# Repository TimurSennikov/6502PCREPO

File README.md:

этот репозиторий был создан для моего друга Ромы, чтобы пояснить ему что и куда паять, если вы про и знаете, что такое конденсатор, можете не читать эту часть README.

###обозначения###

общие:
C - конденсатор (на схеме круг с закрашенной правой половиной), накапливает в себе заряд, в схеме нужен для выпрямления высокочастотных колебаний на микросхемах (0.1uF) и на входе (10uF).

R - резистор/сопротивление (на схеме прямоугольник с выводами из меньших сторон) препятствует протеканию тока U=IR, где U - напряжение, I - сила тока, R - сопротивление, в схеме используется для понижения протекающего за резисторами тока.

SW - переключатель, по сути просто кнопка.

D (LED) - светодиод, в схеме их 3, первый светится всегда, когда есть питание, второй при чтении, третий при записи.

прочие:
J1 - место для разъёма питания.

U1 - CPU (6502/65C02).

U2 - RAM (AS6C4008-55PCN).

U3 - микросхема логики (содержит 4 NAND гейта).

U4 - линейный стабилизатор напряжения.

U5 - хз куда она делась, её нет на схеме, лол.

U6 - ROM (27C512).

U7 - reset контроллер (DS813-5+).

X1 - кварцевый резонатор (1мГц).

Рома прочитай это.

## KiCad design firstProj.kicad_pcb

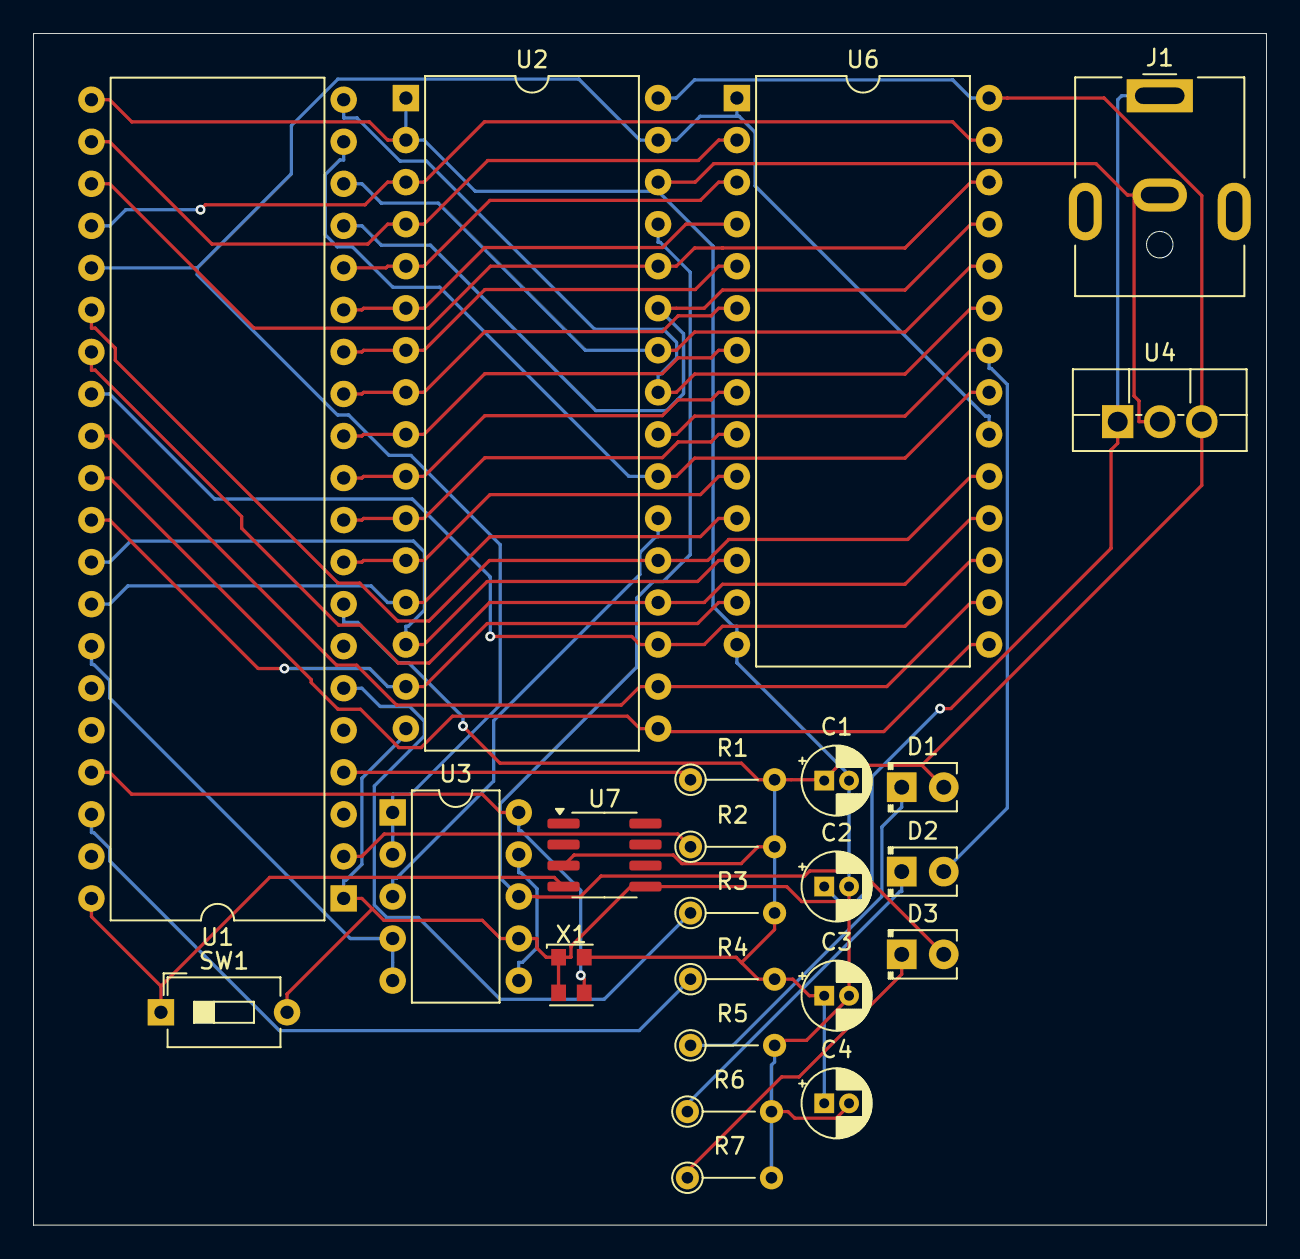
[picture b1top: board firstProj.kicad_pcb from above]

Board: 2 copper layers, 74.5 x 72.0 mm, 23 parts (0 on the bottom side), 41 nets.

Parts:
C1, C3, C4: 0.1uF; CP_Radial_D4.0mm_P1.50mm
C2: 10uF; CP_Radial_D4.0mm_P1.50mm
D1, D2, D3: LED; LED_D2.0mm_W4.0mm_H2.8mm_FlatTop
J1: Barrel_Jack; BarrelJack_CUI_PJ-063AH_Horizontal
R1, R2, R3, R4: R; R_Axial_DIN0204_L3.6mm_D1.6mm_P5.08mm_Vertical
R5, R6, R7: 220; R_Axial_DIN0204_L3.6mm_D1.6mm_P5.08mm_Vertical
SW1: SW_Push; SW_DIP_SPSTx01_Slide_6.7x4.1mm_W7.62mm_P2.54mm_LowProfile
U1: 6502; DIP-40_W15.24mm
U2: AS6C4008-55PCN; DIP-32_W15.24mm
U3: 74HC00; DIP-10_W7.62mm
U4: L7805; TO-220F-3_Vertical
U6: 27C512; DIP-28_W15.24mm
U7: DS813-5+; SOIC-8_3.9x4.9mm_P1.27mm
X1: 1 MHz; Oscillator_SMD_EuroQuartz_XO32-4Pin_3.2x2.5mm

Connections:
+5V: C1.1, C3.1, C4.1, D1.2 (A), R1.2, R2.2, R3.2, R4.2, U1.8 (VCC), U2.32 (VCC), U4.3 (OUT), U6.28 (VCC), U7.3 (V_{DD}), X1.4 (V+)
A0: U1.9 (A0), U2.12 (A0), U6.10 (A0)
A1: U1.10 (A1), U2.11 (A1), U6.9 (A1)
A2: U1.11 (A2), U2.10 (A2), U6.8 (A2)
A3: U1.12 (A3), U2.9 (A3), U6.7 (A3)
A4: U1.13 (A4), U2.8 (A4), U6.6 (A4)
A5: U1.14 (A5), U2.7 (A5), U6.5 (A5)
A6: U1.15 (A6), U2.6 (A6), U6.4 (A6)
A7: U1.16 (A7), U2.5 (A7), U6.3 (A7)
A8: U1.17 (A8), U2.27 (A8), U6.25 (A8)
A9: U1.18 (A9), U2.26 (A9), U6.24 (A9)
A10: U1.19 (A10), U2.23 (A10), U6.21 (A10)
A11: U1.20 (A11), U2.25 (A11), U6.23 (A11)
A12: U1.22 (A12), U2.4 (A12), U6.2 (A12)
A13: U1.23 (A13), U2.28 (A13), U6.26 (A13)
A14: U1.24 (A14), U2.3 (A14), U6.27 (A14)
A15: U1.25 (A15), U2.31 (A15), U3.1, U3.2, U6.1 (A15), U6.20 (~CE)
CLOCK: U1.37 (ϕ0), U3.10, X1.3 (OUT)
D0: U1.33 (D0), U2.13 (DQ0), U6.11 (D0)
D1: U1.32 (D1), U2.14 (DQ1), U6.12 (D1)
D2: U1.31 (D2), U2.15 (DQ2), U6.13 (D2)
D3: U1.30 (D3), U2.17 (DQ3), U6.15 (D3)
D4: U1.29 (D4), U2.18 (DQ4), U6.16 (D4)
D5: U1.28 (D5), U2.19 (DQ5), U6.17 (D5)
D6: U1.27 (D6), U2.20 (DQ6), U6.18 (D6)
D7: U1.26 (D7), U2.21 (DQ7), U6.19 (D7)
GND: C1.2, C2.2, C3.2, C4.2, J1.2, R5.2, R6.2, R7.2, SW1.2, U1.1 (VSS), U1.21 (VSS), U2.1 (A18), U2.2 (A16), U2.16 (VSS), U2.30 (A17), U3.7 (GND), U4.2 (GND), U6.14 (GND), U7.5 (GND), X1.1 (EN), X1.2 (GND)
MA15: U2.22 (CE#), U3.3
unnamed: D1.1 (K), R5.1
unnamed: D2.1 (K), R6.1
unnamed: D3.1 (K), R7.1
unnamed: R2.1, U1.2 (RDY)
unnamed: R1.1, U1.4 (~IRQ)
unnamed: R3.1, U1.6 (~NMI)
unnamed: R4.1, U1.38 (~SO)
unnamed: U3.6, U3.9
unnamed: C2.1, J1.1, U4.1 (IN)
RD: D2.2 (A), U2.24 (OE#), U6.22 (~OE)
RES: SW1.1, U1.40 (~RES), U7.4 (DQ)
RW: U1.34 (R/~W), U3.4, U3.5
WR: D3.2 (A), U2.29 (WE#), U3.8
